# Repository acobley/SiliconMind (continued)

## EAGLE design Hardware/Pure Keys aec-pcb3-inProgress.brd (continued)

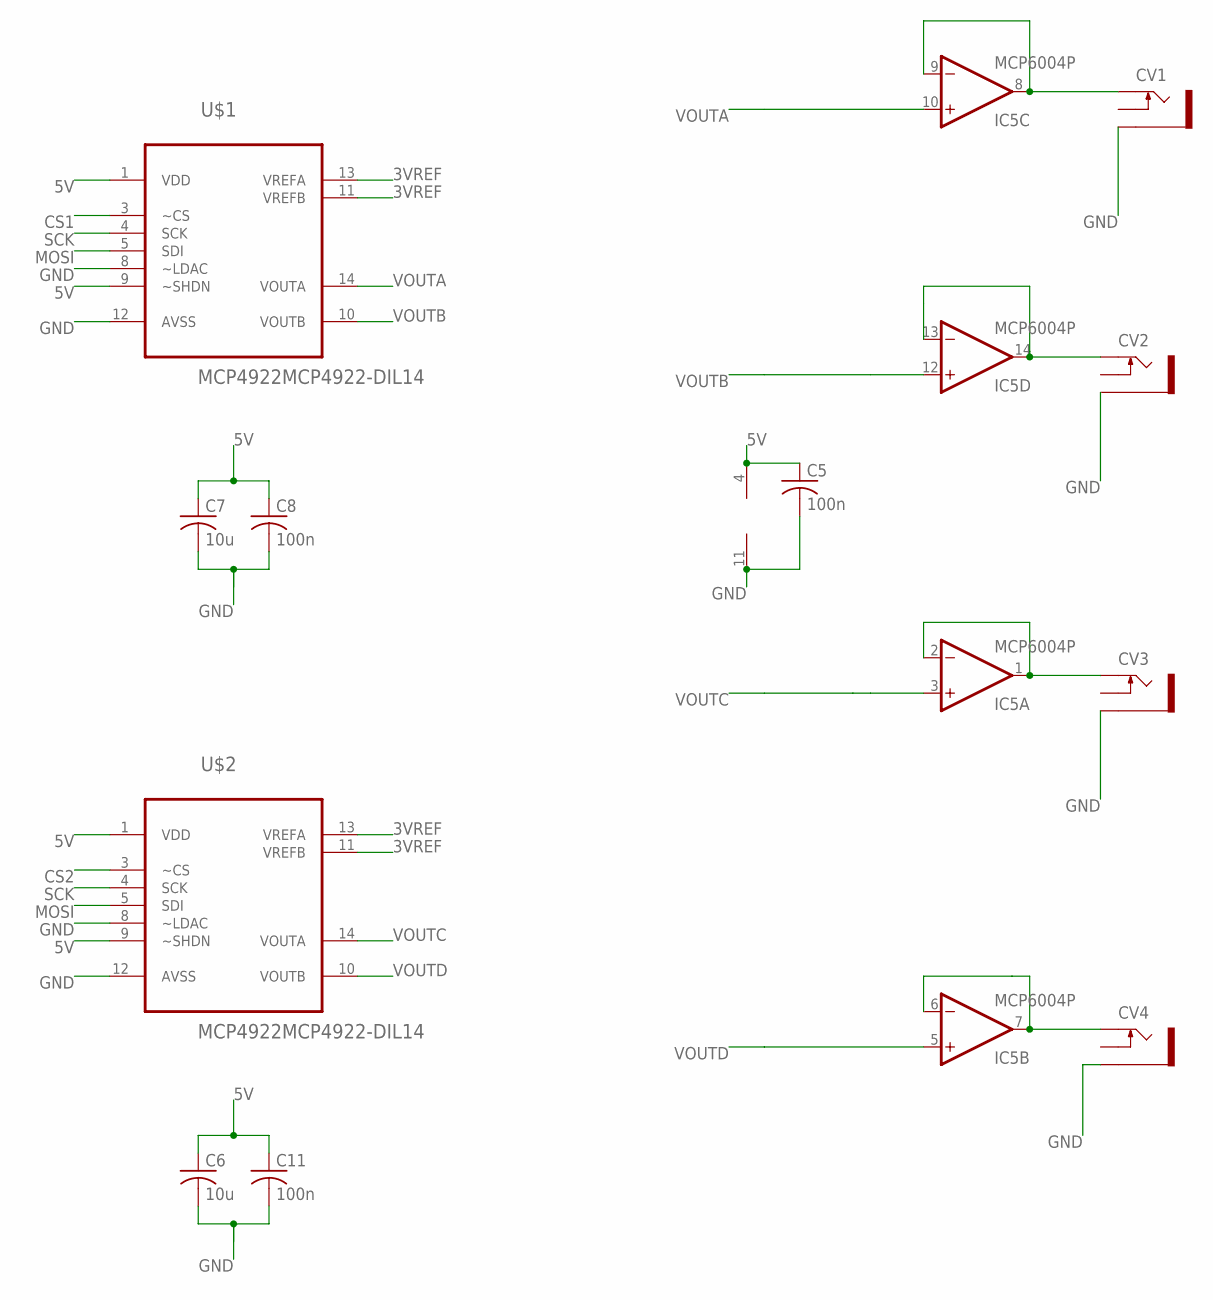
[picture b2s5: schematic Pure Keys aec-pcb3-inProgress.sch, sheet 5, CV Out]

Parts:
C5, C8, C11: 100n; C0805K
C6, C7: 10u; C0805K
CV1, CV2, CV3, CV4: PJ302M
IC5: MCP6004P; DIL14
U$1, U$2: MCP4922MCP4922-DIL14; DIL14

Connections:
3VREF: U$1.11 (VREFB), U$1.13 (VREFA), U$2.11 (VREFB), U$2.13 (VREFA); also elsewhere on the board
5V: C5.1, C6.1, C7.1, C8.1, C11.1, IC5.4 (V+), U$1.1 (VDD), U$1.9 (~SHDN), U$2.1 (VDD), U$2.9 (~SHDN); also elsewhere on the board
CS1: U$1.3 (~CS); also elsewhere on the board
CS2: U$2.3 (~CS); also elsewhere on the board
GND: C5.2, C6.2, C7.2, C8.2, C11.2, CV1.GND (SLEEVE), CV2.GND (SLEEVE), CV3.GND (SLEEVE), CV4.GND (SLEEVE), IC5.11 (V-), U$1.8 (~LDAC), U$1.12 (AVSS), U$2.8 (~LDAC), U$2.12 (AVSS); also elsewhere on the board
MOSI: U$1.5 (SDI), U$2.5 (SDI); also elsewhere on the board
unnamed: CV1.TIP, IC5.8 (OUT), IC5.9 (-IN)
unnamed: CV4.TIP, IC5.6 (-IN), IC5.7 (OUT)
unnamed: CV3.TIP, IC5.1 (OUT), IC5.2 (-IN)
unnamed: CV2.TIP, IC5.13 (-IN), IC5.14 (OUT)
SCK: U$1.4 (SCK), U$2.4 (SCK); also elsewhere on the board
VOUTA: IC5.10 (+IN), U$1.14 (VOUTA)
VOUTB: IC5.12 (+IN), U$1.10 (VOUTB)
VOUTC: IC5.3 (+IN), U$2.14 (VOUTA)
VOUTD: IC5.5 (+IN), U$2.10 (VOUTB)

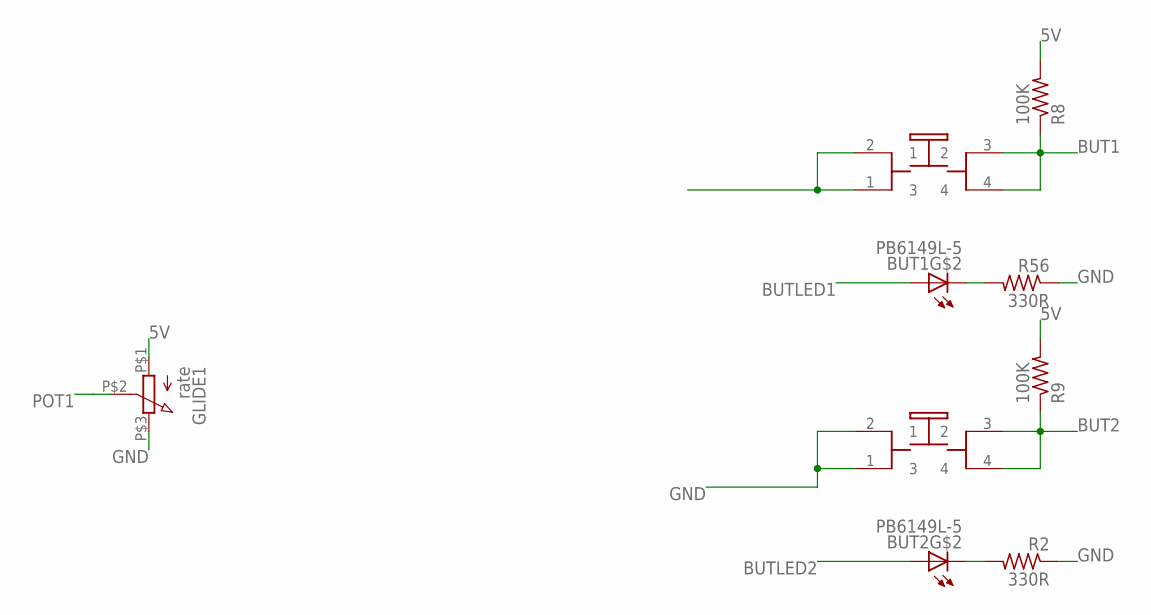
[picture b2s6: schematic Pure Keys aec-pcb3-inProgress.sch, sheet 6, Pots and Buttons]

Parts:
BUT1, BUT2: PB6149L-5; PB6149L
GLIDE1: rate; POT
R2, R56: 330R; R0805
R8, R9: 100K; R0805

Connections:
5V: GLIDE1.P$1 (1), R8.2, R9.2; also elsewhere on the board
BUT1: BUT1.3 (2), BUT1.4, R8.1; also elsewhere on the board
BUT2: BUT2.3 (2), BUT2.4, R9.1; also elsewhere on the board
BUTLED1: BUT1.A; also elsewhere on the board
BUTLED2: BUT2.A; also elsewhere on the board
GND: BUT1.1 (3), BUT1.2 (1), BUT2.1 (3), BUT2.2 (1), GLIDE1.P$3 (3), R2.1, R56.1; also elsewhere on the board
unnamed: BUT2.K (C), R2.2
unnamed: BUT1.K (C), R56.2
POT1: GLIDE1.P$2 (2); also elsewhere on the board

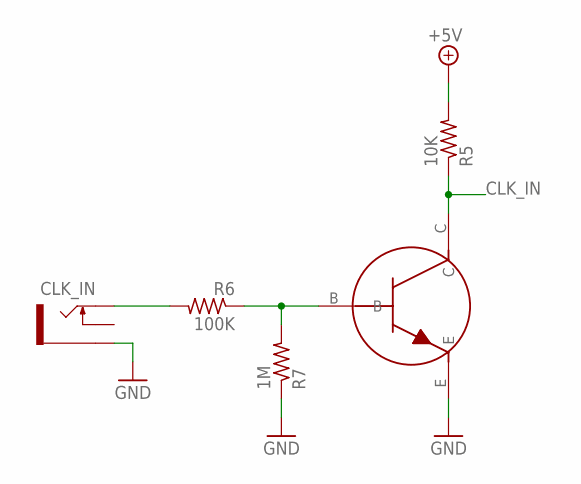
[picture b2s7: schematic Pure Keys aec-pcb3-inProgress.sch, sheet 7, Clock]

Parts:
CLK_IN: PJ302M
R5: 10K; R0805
R6: 100K; R0805
R7: 1M; R0805
T1: 2N3904; TRANSISTOR_SINGLE_N-TYPE

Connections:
5V: R5.2; also elsewhere on the board
CLK_IN: R5.1, T1.C; also elsewhere on the board
GND: CLK_IN.GND (SLEEVE), R7.1, T1.E; also elsewhere on the board
unnamed: R6.1, R7.2, T1.B
unnamed: CLK_IN.TIP, R6.2

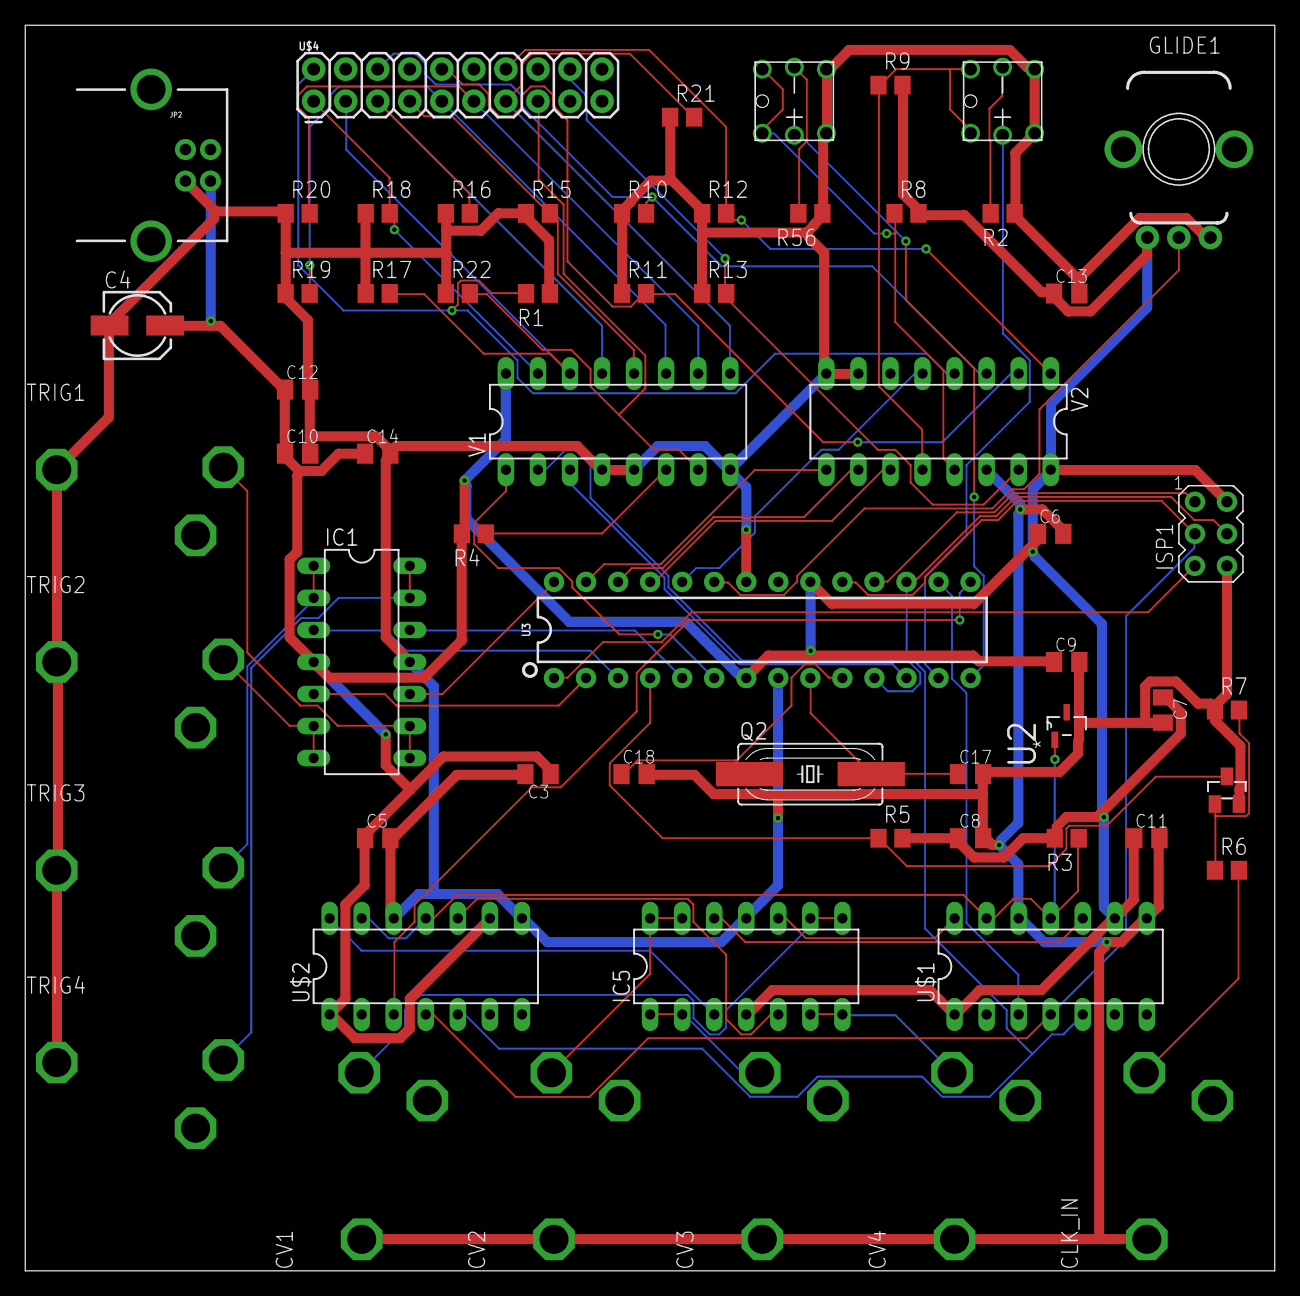
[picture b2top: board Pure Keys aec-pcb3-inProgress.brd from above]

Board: 2 copper layers, 99.0 x 98.7 mm, 61 parts (0 on the bottom side), 58 nets.

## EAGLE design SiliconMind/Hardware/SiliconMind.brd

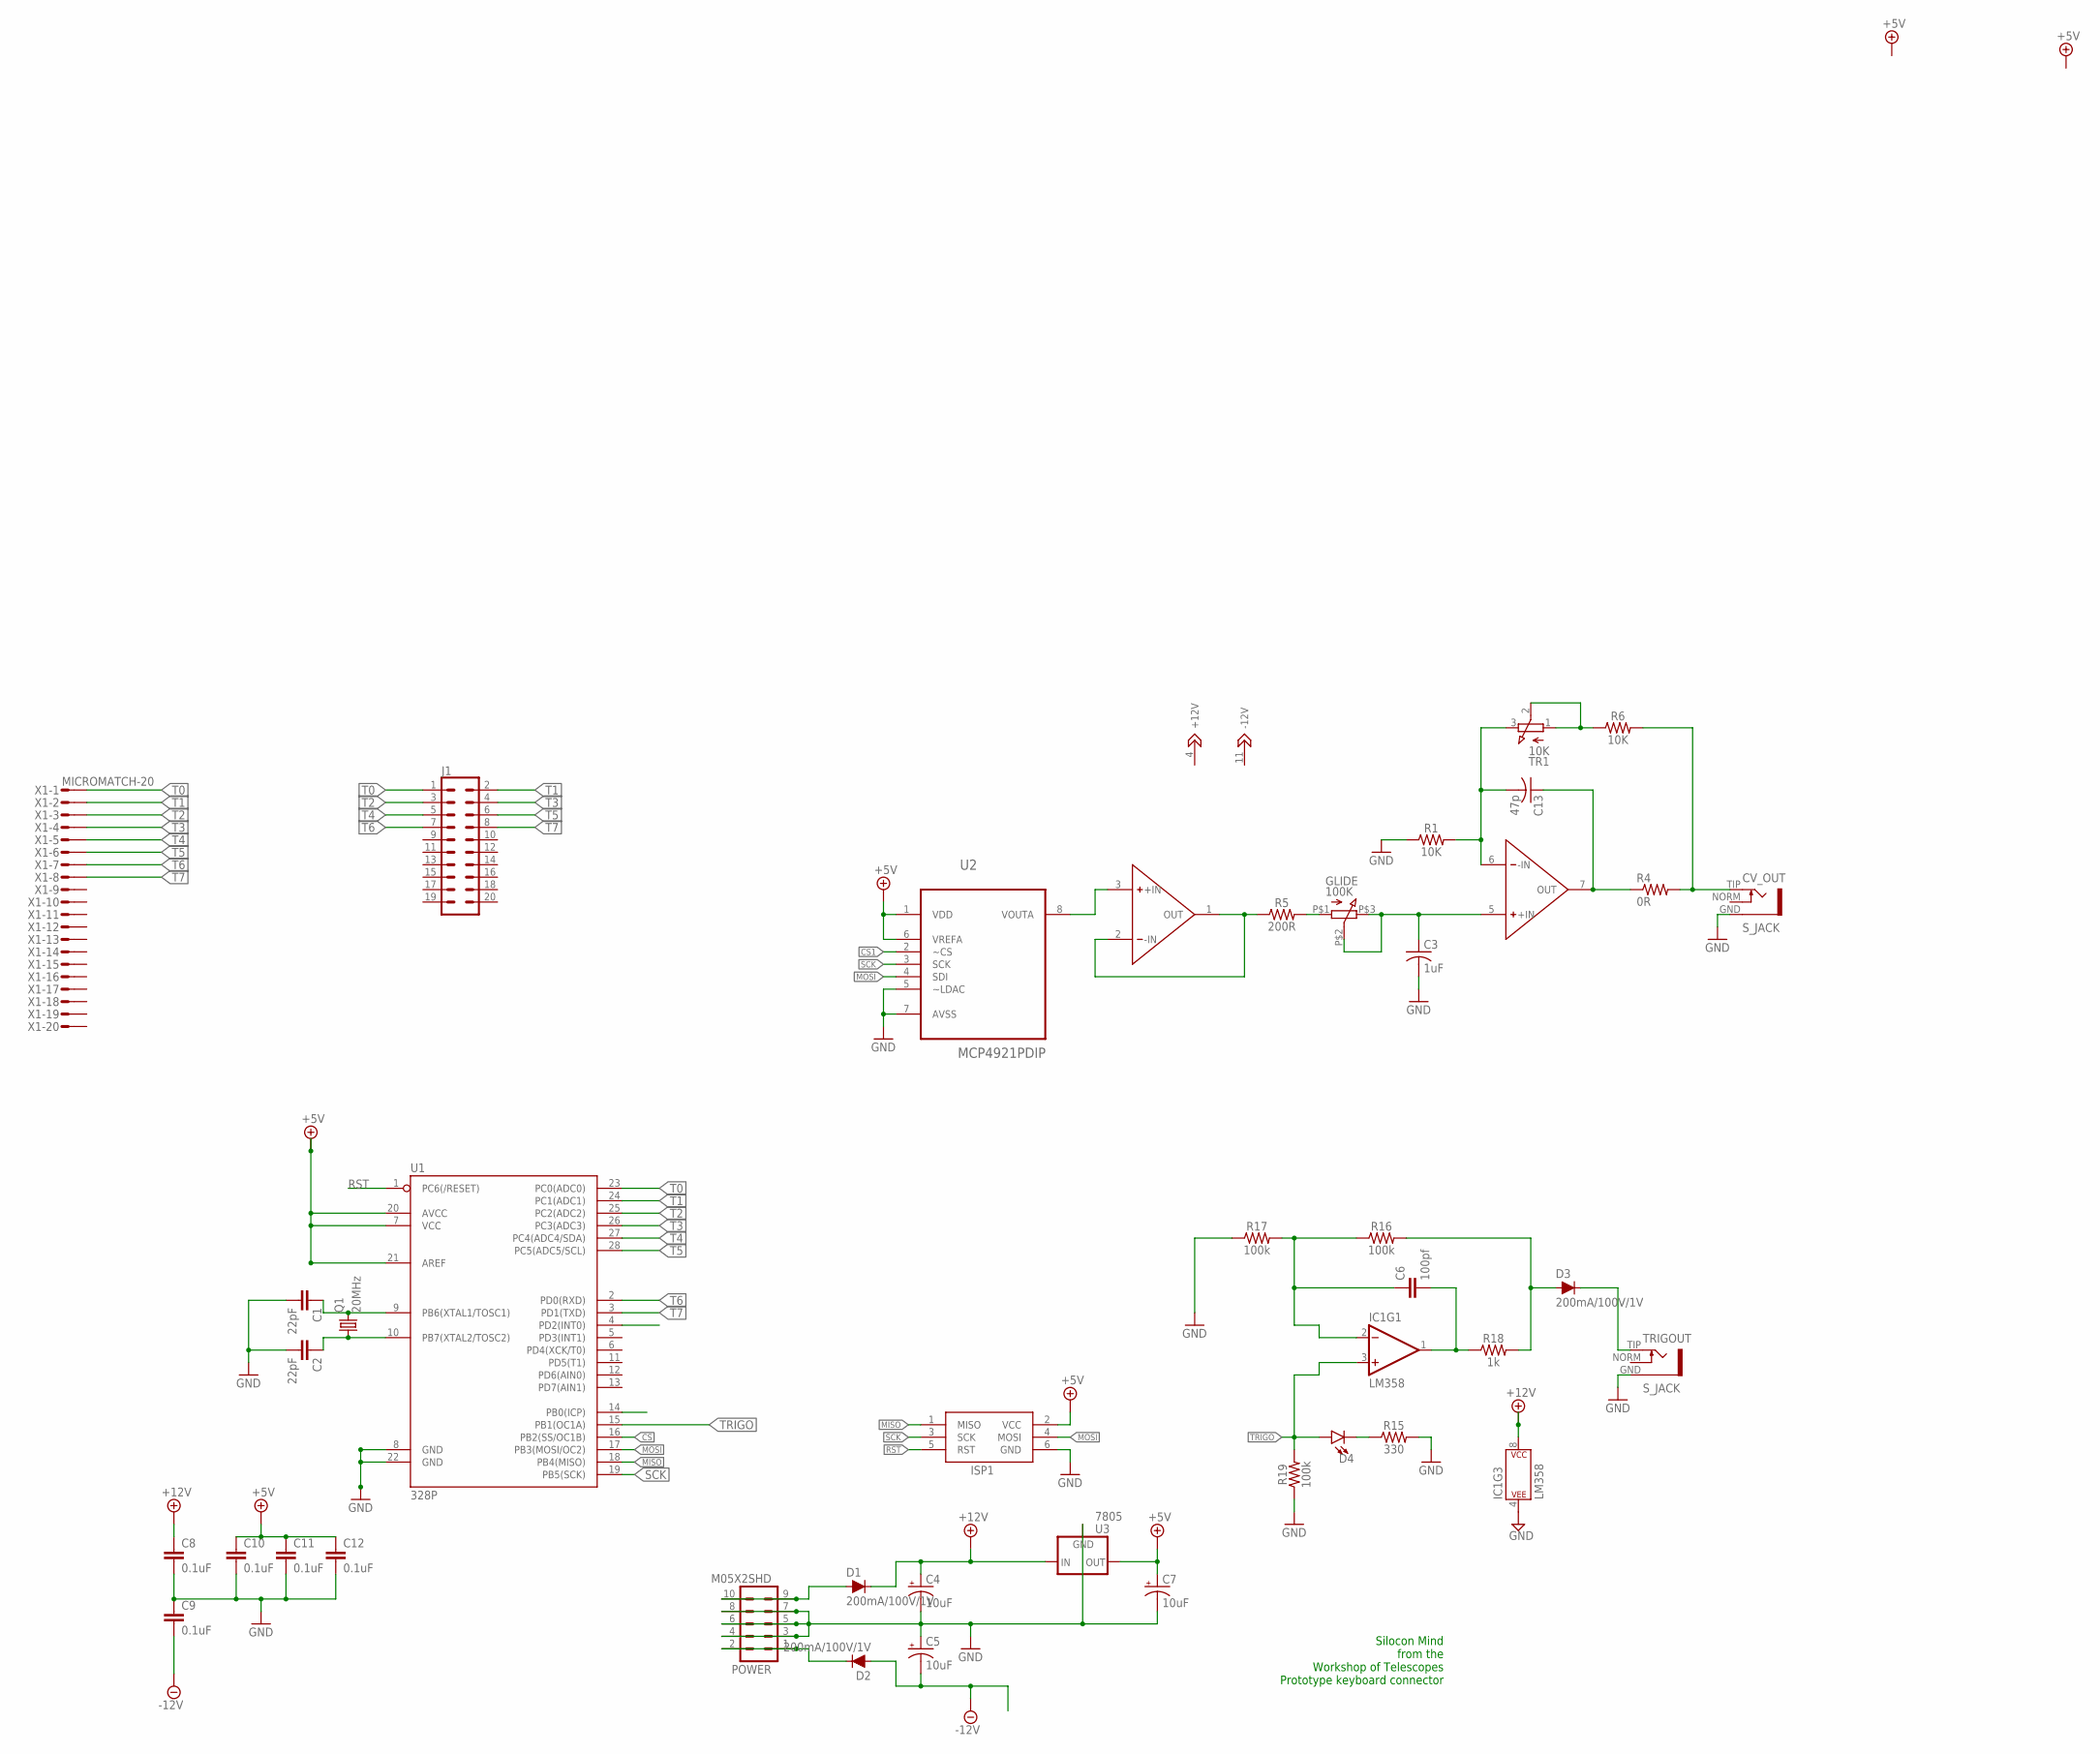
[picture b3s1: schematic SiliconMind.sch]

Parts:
C1, C2: 22pF; CAP-PTH-2.54
C3: 1uF; C0805K
C4, C5, C7: 10uF; CPOL-RADIAL-2.5MM-5MM
C6: 100pf; C075-032X103
C8, C9, C10, C11, C12: 0.1uF; CAP-PTH-SMALL-KIT
C13: 47p; C0805K
CV_OUT: S_JACK
D1, D2, D3: 200mA/100V/1V; DIODE-1N4148
D4: LED3MM; LED_3MM
GLIDE: 100K; Q-POT
IC1: LM358; DIP08
ISP1: AVRISP-6; AVRISP
J1: CONN_10X2; 2X10
POWER: M05X2SHD; 2X5-SHROUDED
Q1: 20MHz; HC49U70
R1, R6: 10K; AXIAL-0.3
R4: 0R; R0805
R5: 200R; AXIAL-0.3
R15: 330; AXIAL-0.3
R16, R17, R19: 100k; AXIAL-0.3
R18: 1k; AXIAL-0.3
TR1: 10K; TRIM_3269W
TRIGOUT: S_JACK
U1: 328P; DIP28
U2: MCP4921PDIP; DIP08
U3: 7805; TO-220-ALT
U4: QUAD_OPAMPDIP14; DIP254P762X533-14
X1: MICROMATCH-20

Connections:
+5V: C7.1 (+), C10.1, C11.1, C12.1, ISP1.2 (VCC), U1.7 (VCC), U1.20 (AVCC), U1.21 (AREF), U2.1 (VDD), U2.6 (VREFA), U3.OUT
+12V: C4.1 (+), C8.1, D1.C, IC1.8 (P$V+), U3.IN
-12V: C5.2 (-), C9.2, D2.A
BUTLED: U1.15 (PB1(OC1A))
CS: U1.16 (PB2(SS/OC1B))
CS1: U2.2 (~CS)
GND: C1.2, C2.2, C3.2, C4.2 (-), C5.1 (+), C7.2 (-), C8.2, C9.1, C10.2, C11.2, C12.2, CV_OUT.GND, IC1.4 (P$V-), ISP1.6 (GND), POWER.3, POWER.4, POWER.5, POWER.6, POWER.7, POWER.8, R1.P$1 (1), R15.P$2 (2), R17.P$1 (1), R19.P$1 (1), TRIGOUT.GND, U1.8 (GND), U1.22 (GND), U2.5 (~LDAC), U2.7 (AVSS), U3.GND
MISO: ISP1.1 (MISO), U1.18 (PB4(MISO))
MOSI: ISP1.4 (MOSI), U1.17 (PB3(MOSI/OC2)), U2.4 (SDI)
unnamed: C1.1, Q1.2, U1.9 (PB6(XTAL1/TOSC1))
unnamed: C2.1, Q1.1, U1.10 (PB7(XTAL2/TOSC2))
unnamed: U2.8 (VOUTA), U4.3 (+IN)
unnamed: R5.P$1 (1), U4.1 (OUT), U4.2 (-IN)
unnamed: GLIDE.P$1 (1), R5.P$2 (2)
unnamed: C3.1, GLIDE.P$2 (2), GLIDE.P$3 (3), U4.5 (+IN)
unnamed: R6.P$1 (1), TR1.1, TR1.2
unnamed: CV_OUT.TIP, R4.2, R6.P$2 (2)
unnamed: D1.A, POWER.9, POWER.10
unnamed: D2.C, POWER.1, POWER.2
unnamed: C13.1, R4.1, U4.7 (OUT)
unnamed: C13.2, R1.P$2 (2), TR1.3, U4.6 (-IN)
unnamed: D4.K (C), R15.P$1 (1)
unnamed: C6.1, IC1.2 (-IN), R16.P$1 (1), R17.P$2 (2)
unnamed: C6.2, IC1.1 (OUT), R18.P$1 (1)
unnamed: D3.A, R16.P$2 (2), R18.P$2 (2)
unnamed: D3.C, TRIGOUT.TIP
RST: ISP1.5 (RST), U1.1 (PC6(/RESET))
SCK: ISP1.3 (SCK), U1.19 (PB5(SCK)), U2.3 (SCK)
T0: J1.1, U1.23 (PC0(ADC0)), X1.1
T1: J1.2, U1.24 (PC1(ADC1)), X1.2
T2: J1.3, U1.25 (PC2(ADC2)), X1.3
T3: J1.4, U1.26 (PC3(ADC3)), X1.4
T4: J1.5, U1.27 (PC4(ADC4/SDA)), X1.5
T5: J1.6, U1.28 (PC5(ADC5/SCL)), X1.6
T6: J1.7, U1.2 (PD0(RXD)), X1.7
T7: J1.8, U1.3 (PD1(TXD)), X1.8
TRIGO: D4.A, IC1.3 (+IN), R19.P$2 (2), U1.14 (PB0(ICP))

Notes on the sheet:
Silocon Mind from the Workshop of Telescopes Prototype keyboard connector

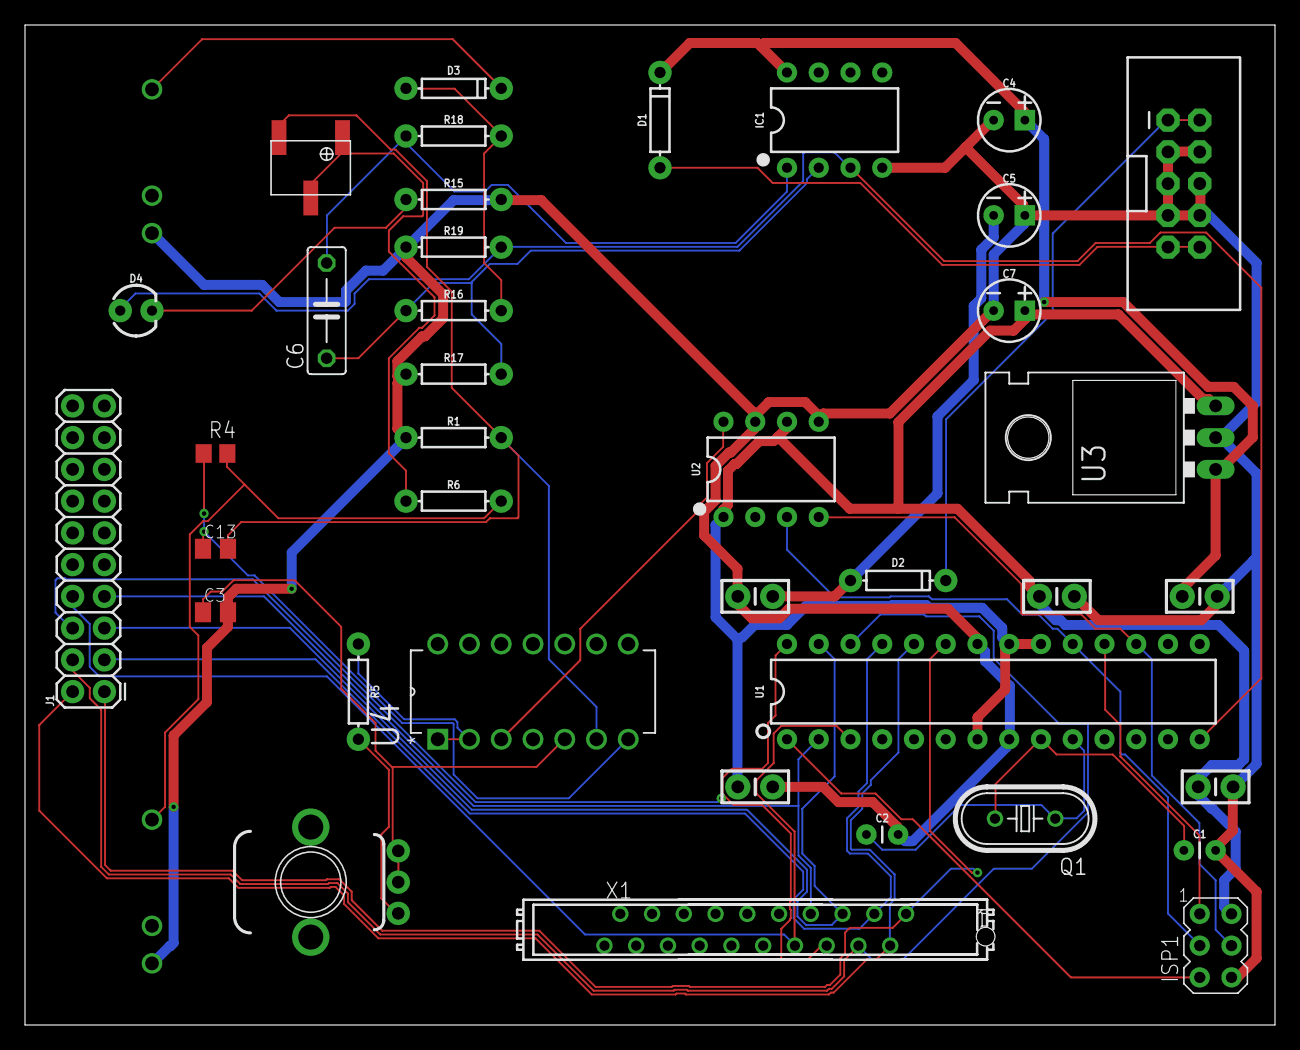
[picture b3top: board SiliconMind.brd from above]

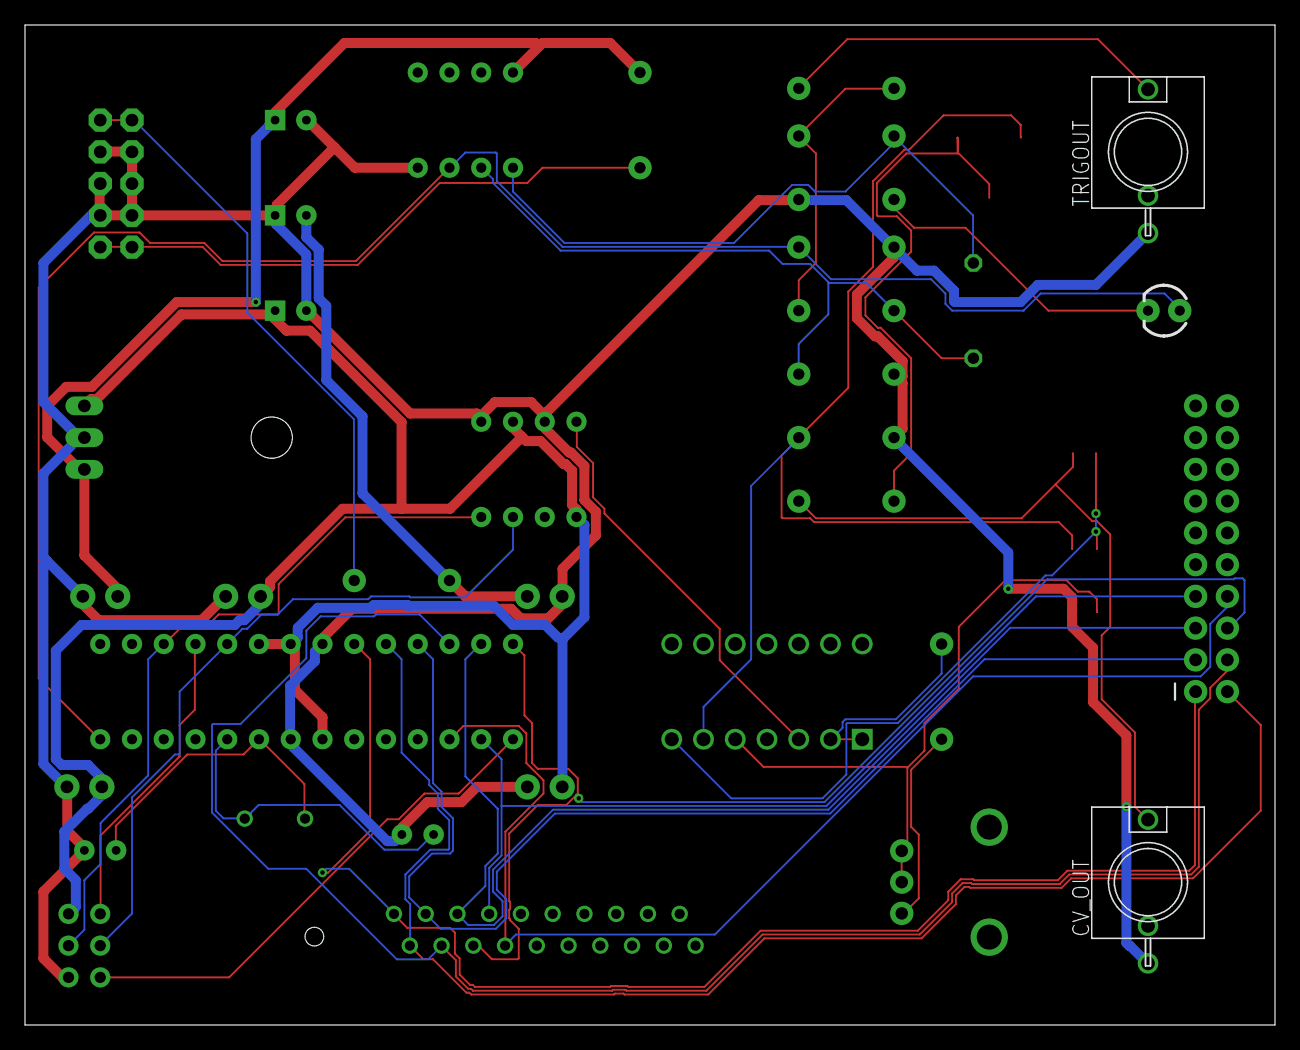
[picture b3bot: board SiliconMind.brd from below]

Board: 2 copper layers, 100.0 x 80.0 mm, 40 parts (2 on the bottom side), 34 nets.

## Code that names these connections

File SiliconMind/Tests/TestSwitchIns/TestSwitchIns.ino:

int ENOUT = 7;
int ENIN = A7;
int DAOUT = 1;
int DBOUT = 0;
int DAIN = A2;
int DBIN = A3;
int AOUT[] = {4, 5, 6};
int AIN[] = {A4, A5, A6};

int BUTLED1 = 5;
int BUTLED2 = 6;

int BUT1 = 6;
int BUT2 = 7;
/*****************
   T0=S8A =Enout + 7
   T1=S7A= Enout + 6
   BUTLED1=SB5
   BUTLED2=SB6
*/
/************************************
   This routine takes a Byte, it writes the bottom Three bits so PD4,PD5,PD6
   as binary

   PD4=A0
   PD5=A1
   PD6=A2
*/


void WriteOutAdd(byte address) {
  address = address - 1;
  for (byte A = 0; A < 3; A++) {
    digitalWrite(AOUT[A], (boolean)(address & 0x01));
    address >>= 1;

  }

}

void WriteInAdd(byte address) {
  address = address - 1;
  for (byte A = 0; A < 3; A++) {
    digitalWrite(AIN[A], (boolean)(address & 0x01));
    address >>= 1;

  }

}


boolean digitalReadPort(int channel, int port) {
  boolean state = false;
  WriteInAdd(port);
  if (channel = DAIN) {
    digitalWrite(ENIN, true);
    if (digitalRead(DAIN) == true)
      state = true;
    digitalWrite(ENIN, false);
  } else {
    digitalWrite(ENIN, true);
    if (digitalRead(DBIN) == true)
      state = true;
    digitalWrite(ENIN, false);

  }
  return state;
}



void setup() {
  // put your setup code here, to run once:

  pinMode(ENOUT, OUTPUT);
  pinMode(ENIN, OUTPUT);

  pinMode(DAOUT, OUTPUT);
  pinMode(DBOUT, OUTPUT);
  pinMode(DAIN, INPUT);
  pinMode(DBIN, INPUT);

  for (byte A = 0; A < 3; A++) {
    pinMode(AOUT[A], OUTPUT);
    pinMode(AIN[A], OUTPUT);
  }
  digitalWrite(ENOUT, false);
  digitalWrite(DBOUT, true);
  //Do some LED flashing
  for (int i = 0; i < 10; i++) {
    digitalWrite(ENOUT, true);
    for (int j = 0; j < 100; j++) {
      WriteOutAdd(BUTLED1);
      delay(1);
      WriteOutAdd(BUTLED2);
      delay(1);
    }

    digitalWrite(ENOUT, false);
    delay(300);
  }
  digitalWrite(DBOUT, false);

}



void loop() {

  boolean sw = digitalReadPort(DAIN, BUT1);
  if (sw == true) {
    WriteOutAdd(BUTLED1);
    digitalWrite(DBOUT, true);
    digitalWrite(ENOUT, true);
  }
  else {
    WriteOutAdd(BUTLED1);
    digitalWrite(DBOUT, false);
    digitalWrite(ENOUT, false);
  }


}

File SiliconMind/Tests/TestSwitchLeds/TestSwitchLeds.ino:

int ENOUT=7;
int DAOUT=1;
int DBOUT=0;
int A0OUT=4;
int A1OUT=5;
int A2OUT=6;

int BUTLED1=5;
int BUTLED2=6;
/*****************
 * T0=S8A =Enout + 7
 * T1=S7A= Enout + 6
 * BUTLED1=SB5 
 * BUTLED2=SB6
 */
/************************************
   This routine takes a Byte, it writes the bottom Three bits so PD4,PD5,PD6
   as binary

   PD4=A0
   PD5=A1
   PD6=A2
*/
int AOUT[] = {4, 5, 6};
void WriteAdd(byte address) {
  address=address-1;
  for (byte A = 0; A < 3; A++) {
    digitalWrite(AOUT[A], (boolean)(address & 0x01));
    address >>= 1;

  }

}

void setup() {
  // put your setup code here, to run once:

  pinMode(ENOUT, OUTPUT);
  pinMode(DAOUT, OUTPUT);
  pinMode(DBOUT, OUTPUT);
  for (byte A = 0; A < 3; A++) {
    pinMode(AOUT[A], OUTPUT);
  }
  digitalWrite(ENOUT, false);
  digitalWrite(DBOUT, true);
  WriteAdd(BUTLED2); 

  digitalWrite(ENOUT, true);
  delay(2000);
}



void loop() {
 WriteAdd(BUTLED1); 
 digitalWrite(DBOUT, true);
  digitalWrite(ENOUT, true);
  delay(100);
  digitalWrite(ENOUT, false);
  WriteAdd(BUTLED2); 
  digitalWrite(ENOUT, true);
  delay(100);
  digitalWrite(ENOUT, false);
  delay(500);
  

}

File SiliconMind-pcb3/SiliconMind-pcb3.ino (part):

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
int DACS[2] = {10, 10};
byte AIN[] = {A2, A3, A4};
int ButLED1 = 8;
int ButLED2 = 7;
int ButLED3 = 9;
int LEDS[3] = {8, 7, 9};

volatile int LedFlashCount1 = 0;
volatile int LedFlashCount2 = 0;
int But1 = 6;
int But2 = 7;
int But3 = 5;
boolean But1State = false;
boolean But2State = false;
boolean But3State = false;
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int LowKeyOffset = 0;
int mode = MONO;
int CurrentPoly = 4;
int DAIN = A1;
int DBIN = A0;
float PortRate = 0.25; //Initial Portemantau rate
float Range = 1365.333; // (2^12/3)

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    CurrentPoly = 2;
  else if (mode == POLY)
    CurrentPoly = MaxPoly;
  pinMode(ButLED1, OUTPUT);
  pinMode(ButLED2, OUTPUT);
  pinMode(ButLED3, OUTPUT);
  digitalWrite(ButLED1, HIGH);
  digitalWrite(ButLED2, HIGH);
  digitalWrite(ButLED3, HIGH);
  pinMode(DAIN, INPUT);
  pinMode(DBIN, INPUT);
  SPI.begin();
  SPI.setBitOrder(MSBFIRST);
  delay(500);
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
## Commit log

2017-10-28 added arduino code
2017-11-02 First hardware layout
2017-11-02 Software template
2017-11-02 Board Template added
2017-11-03 added micro match connector
2017-11-03 Changed TL074 to TTL
2017-11-09 added IDC connector
2017-11-12 first working PoC
2017-11-14 updated Vout calculation
2017-11-14 Low note Priority added
2017-11-14 Now high note priority
2017-11-14 removed voltage table
2017-11-19 Towards Duiphonic
2017-11-19 Towards PolyPhonic
2017-11-19 Mono and Split working, Poly a bit iffy
2017-11-22 temp push while sort is fixed
2017-11-22 temp push while sort is fixed 2
2017-11-23 Polyphonci v1
2018-01-01 First push of new branch
2018-02-05 My version of the board using TTL logic for mux/demux. Also removed the clock out and reduced boeard size to keep cost down
2018-02-05 Added some tests
2018-02-05 My Board
2018-02-05 removed old board
2018-02-05 Added Tests
2018-02-05 Slight update
2018-02-06 Changed MUX/DEMUX connections and removed one POT
2018-02-06 added back plane
2018-03-03 added test for DACS
2018-03-04 added pcb1 borad and schematic THis borad has a TL072 on it that is NOT needed. Left over form clock in
2018-03-04 added in progress board and change log
2018-03-07 updated in progress board added text layer text added classes for power rerouted
2018-03-07 Added dxf file for tcream
2018-03-07 reroute
2018-03-07 added illustrator file for stencil
2018-03-13 updated board and tests
2018-03-13 added tests for AEC board
2018-03-14 more AEC tests
2018-03-15 changed 74238 for 74138
2018-03-15 Notes TDB in changelog
2018-03-16 updated switches on in progress
2018-03-16 updated changelog
2018-03-18 GMSN tests updated
2018-03-19 updated code to PCB 1
2018-03-19 Updated software
2018-03-19 Updated routing on in-progress board to make room for 1K pull downs
2018-03-19 Added tests to GMSN! board
2018-03-20 updated code to handle multiple DACS
2018-03-20 changed in progress board
2018-03-20 updated READ.MD
2018-03-21 changed pcb2-in-progress with ne layout of MK resistors
2018-03-21 added PCB 2
2018-03-22 update split mode num
2018-03-27 Backlink to CADLAB.io has been added.
2018-03-27 Added pcb3-inProgress
2018-03-29 adding part numbers to attributes
2018-03-29 routing on pcb-3-inprogress
2018-03-29 Updated vesion message
2018-04-08 updated to PSB 2
2018-04-09 Split mode code working
2018-04-09 Poly mode switch working
2018-04-09 Portamento mode in mono and poly mode
2018-04-12 Added record switch fucntionality (not recording)
2018-04-13 record mode working
2018-04-16 Save to Eprom works, splt mode broken, crashes if you play keyboard and sequence at the same time
2018-04-17 Save to Eprom works, splt mode broken
2018-04-17 Save to Eprom works
2018-04-24 polyphonic broken
2018-04-24 First Attempt at fixing poly mode to stick keys
2018-04-24 Added gate on
2018-04-26 Legato mode
2018-04-26 minor comment update
2018-04-27 Mono and Split use simple assign voices
2018-04-29 removed legato debounce
2018-04-30 minor upate
2018-05-26 minor update
2018-07-22 Pixed Port rate
2018-07-23 Update comment text for portamento
2018-07-23 minor comment changes
2018-07-23 changed write notes
2018-07-24 fixed split mode
2018-07-24 Added portamento to split
2018-07-26 Added Pcb3 SMD
2018-07-26 changed cs select
2018-07-27 New Board Shape and layout
2018-07-27 THinner board
2018-07-28 reroutes
2018-07-28 Removed voltage class for SMD
2018-07-28 Moved text on rear
2018-07-29 Replaced Sockets with vertical type
2018-07-29 Added a SMD with Vertical Pots
2018-07-29 ground plane
2018-07-29 updated Play mode
2018-07-29 updated Play mode for split
2018-07-30 Split mode now aslo sends bass note to output 4
2018-07-30 added Pcb3 in manufacture
2018-08-01 change to pcb3 brd
2018-08-01 Added RS Parts to Semicnductors
2018-08-01 Added excel parts list
2018-08-01 Fixed mistake in attribute of invertor
2018-08-01 Split mode portamanto fix
2018-08-02 Trying note length record
2018-08-31 Always send bass note to out 4 in split mode
2018-09-24 added BOM
2019-01-29 added tests for PCB3
2019-02-18 Updated chaneg log
2019-03-10 updated tests
2019-03-13 added PCB 4
2019-03-13 added dacs and gates test
2019-03-13 updated velocity test
2019-03-13 added Switch test
2019-03-15 tried new board layout
2019-03-18 added clock test
2019-03-18 Software for PCB3
2019-03-19 changed mode order
2019-03-20 Moved pcb3 test to pcb3
2019-03-20 using the Gate pot
2019-03-20 Play and record buttons (Need debouncing)
2019-03-20 Fixed Play LED (Need debouncing)
